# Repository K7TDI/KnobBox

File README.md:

# KnobBox
K7TDI's hardware interface for SDR software

This is a hardware controller for SDR software such as SDR-Console and HDSDR.  It currently utilizes keyboard emulation for input into the software, but the goal of the project is to be entirely compatible with Kenwood CAT serial communication.  This is well implemented in SDR-Console, which is quickly becoming my favorite software to use.  However, by using an Adruino Pro Micro (Atmel 328p, compatible with the Leonardo), keyboard and mouse wheel emulation is easy, and this allows the KnobBox to be used with any software that supports those.

This project, aside from the PCB, uses all off the shelf hardware, most of it available from China on eBay.  The total cost if you go that route is around $30, depending on how many extra parts you order.

It consists of:

An Arduino Pro Micro

2 5 pin rotary encoders with push buttons

a 16x2 LCD display with HD44780 controller

An enclosure

A custom PCB

Some videos:
https://vimeo.com/150329712

https://vimeo.com/150324509

https://vimeo.com/150324508

https://vimeo.com/150324507

**Notice/Current issues**

This is NOT complete, and is a pain to assemble.  I've included issues and proposed fixes in the hardware folder.

The software is also completely incomplete.  This is addressed in the software folder.

I really hope to get feedback and help with this project.  I've been plugging away at it for months now, and learning a lot along the way.  I'm a masters student in health sciences with an undergrad in biology, I hope some of you that are more experienced with hardware design and especially coding will make contributions.

I hope you find what I've released here helpful, and at least a starting point for your own ideas.

If you like this and use it for your own project that you distribute, I'd appreciate it if you included a mention of my callsign (K7TDI) and a link to this repo.

**If you'd like to contact me:**
**k7tdi@technotechnician.com**

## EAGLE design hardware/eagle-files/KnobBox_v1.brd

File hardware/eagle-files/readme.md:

Here are the Eagle files for the KnobBox.  You'll also find my Eagle library here.  Go back and read the readme in the Hardware folder if you haven't yet.

About making the board:

I successfully made this using the toner transfer method with a Brother laser printer, HP photo paper, and Radio Shack etchant solution.  I haven't tried using any other printer, but at least with this combo, after printing I need to put the photo paper in a sealed container containing a little bit of acetone (not touching the paper) for about half an hour before I iron the paper onto the PCB.

I'm still getting the hang of all of it, so I tried to keep the traces as wide and widely spaced as possible.  I'm fairly sure these files are not within spec for production by a board house, but I'm sure it wouldn't be too hard to fix, and some awesome improvements in routing could be made with closer spaced traces and a ground plane.

These files are released under the GPL V3, info can be found in the LICENCE file

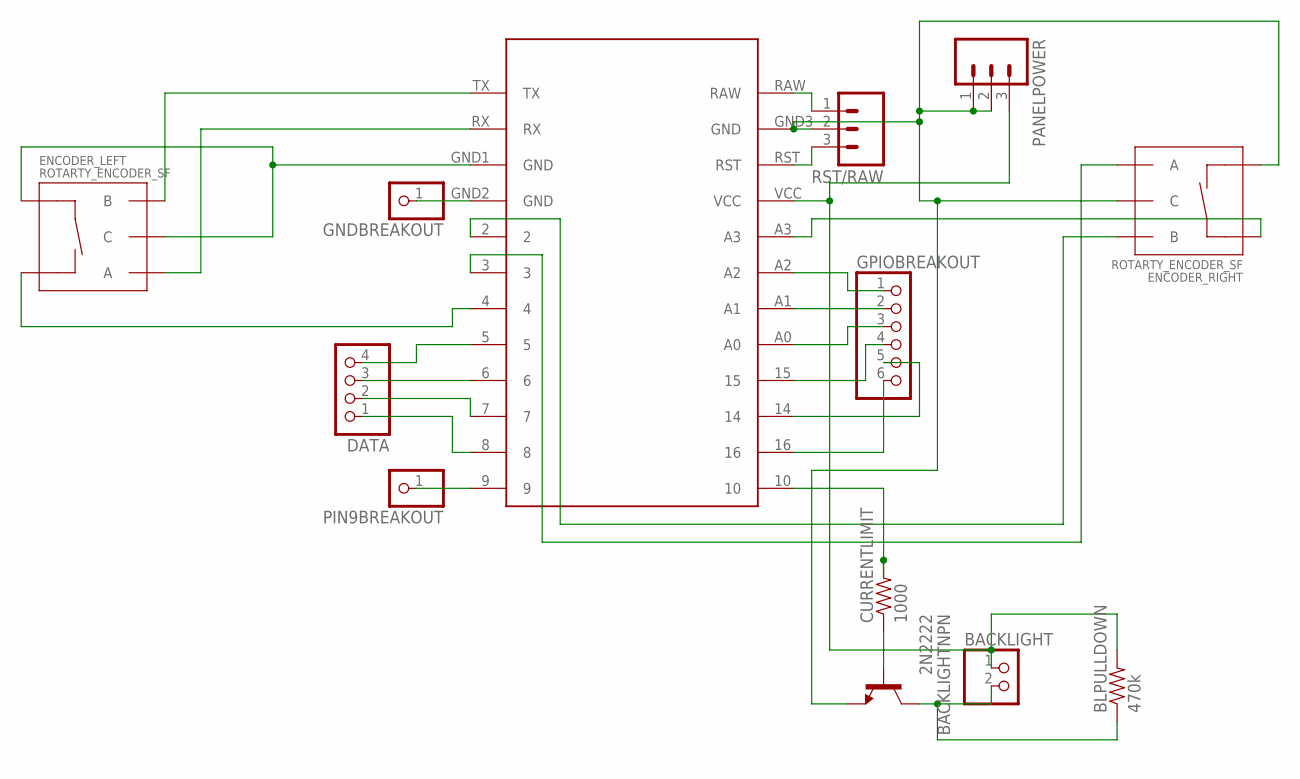
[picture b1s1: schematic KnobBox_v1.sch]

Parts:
BACKLIGHT: PINHD-1X2; 1X02
BACKLIGHTNPN: 2N2222; TO92-EBC-OVAL
BLPULLDOWN: 470k; AXIAL-0.4
CURRENTLIMIT: 1000; AXIAL-0.4
DATA: PINHD-1X4; 1X04
ENCODER_LEFT: ROTARTY_ENCODER_SF; ROTARY_ENC_SF_MOD
ENCODER_RIGHT: ROTARTY_ENCODER_SF; ROTARY_ENC_SF_MOD
GNDBREAKOUT: PINHD-1X1BIG; 1X01_MOD
GPIOBREAKOUT: PINHD-1X6; 1X06
PANELPOWER: M03PTH; 1X03
PIN9BREAKOUT: PINHD-1X1BIG; 1X01_MOD
PROMICRO: PROMICROROUND; PROMICRO
RST/RAW: M03PTH; 1X03

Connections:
unnamed: ENCODER_LEFT.B, PROMICRO.TX
unnamed: ENCODER_LEFT.A, PROMICRO.RX
unnamed: ENCODER_RIGHT.A, PROMICRO.3
unnamed: ENCODER_RIGHT.B, PROMICRO.2
unnamed: BACKLIGHTNPN.E, ENCODER_RIGHT.C, ENCODER_RIGHT.SW-, PANELPOWER.1, PANELPOWER.2, PROMICRO.GND3 (GND), RST/RAW.2
unnamed: ENCODER_LEFT.C, ENCODER_LEFT.SW+, PROMICRO.GND1 (GND)
unnamed: ENCODER_LEFT.SW-, PROMICRO.4
unnamed: ENCODER_RIGHT.SW+, PROMICRO.A3
unnamed: DATA.4, PROMICRO.5
unnamed: DATA.3, PROMICRO.6
unnamed: DATA.2, PROMICRO.7
unnamed: DATA.1, PROMICRO.8
unnamed: CURRENTLIMIT.P$2 (2), PROMICRO.10
unnamed: BACKLIGHTNPN.B, CURRENTLIMIT.P$1 (1)
unnamed: BACKLIGHT.1, BLPULLDOWN.P$2 (2), PANELPOWER.3, PROMICRO.VCC
unnamed: BACKLIGHT.2, BACKLIGHTNPN.C, BLPULLDOWN.P$1 (1)
unnamed: GPIOBREAKOUT.1, PROMICRO.A2
unnamed: GPIOBREAKOUT.2, PROMICRO.A1
unnamed: GPIOBREAKOUT.3, PROMICRO.A0
unnamed: GPIOBREAKOUT.4, PROMICRO.15
unnamed: GPIOBREAKOUT.5, PROMICRO.14
unnamed: GPIOBREAKOUT.6, PROMICRO.16
unnamed: PIN9BREAKOUT.1, PROMICRO.9
unnamed: PROMICRO.RAW, RST/RAW.1
unnamed: PROMICRO.RST, RST/RAW.3
unnamed: GNDBREAKOUT.1, PROMICRO.GND2 (GND)

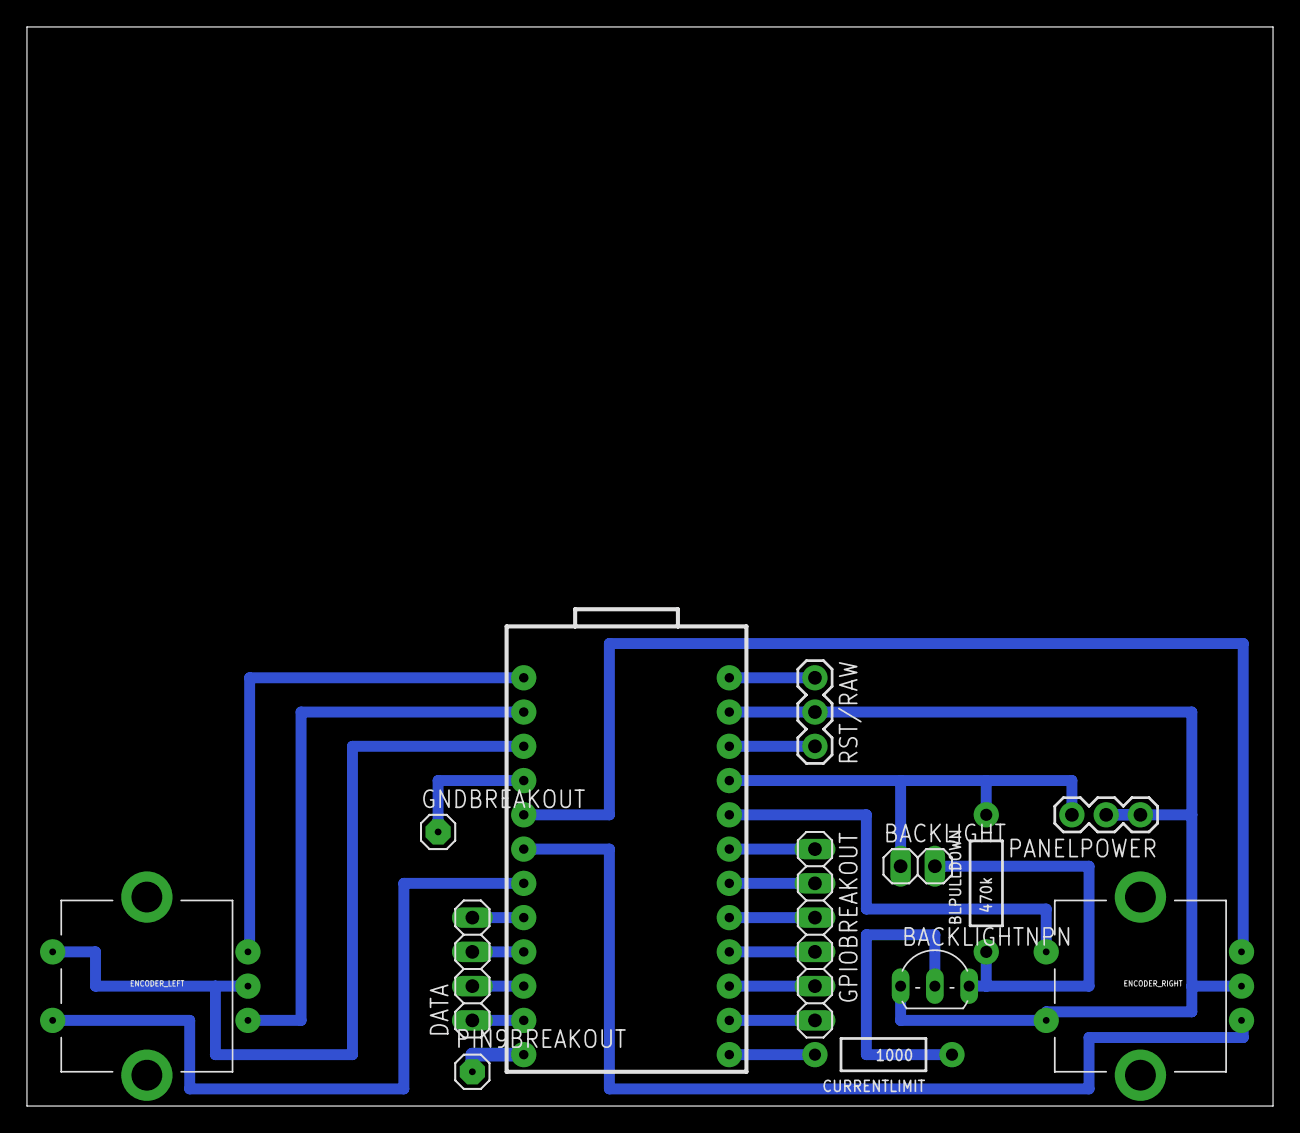
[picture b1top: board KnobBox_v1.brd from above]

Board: 2 copper layers, 92.4 x 80.0 mm, 13 parts (0 on the bottom side), 26 nets.

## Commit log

2015-12-29 adding files
2015-12-29 fixed spacing
2015-12-29 fixed formatting
2015-12-29 first software commit
2015-12-30 first hardware commit
2015-12-30 added licence info
2016-01-31 Update README.md
    added video links
2016-01-31 Update README.md
    fixed video links

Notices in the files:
parts and their libraries:
SparkFun-Passives: Licensing: Creative Commons ShareAlike 4.0 International - https://creativecommons.org/licenses/by-sa/4.0
